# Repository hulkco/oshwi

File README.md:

# Oshwi Badege
This badge is still under development, there are still errors or omissions in the circuit, help is welcome

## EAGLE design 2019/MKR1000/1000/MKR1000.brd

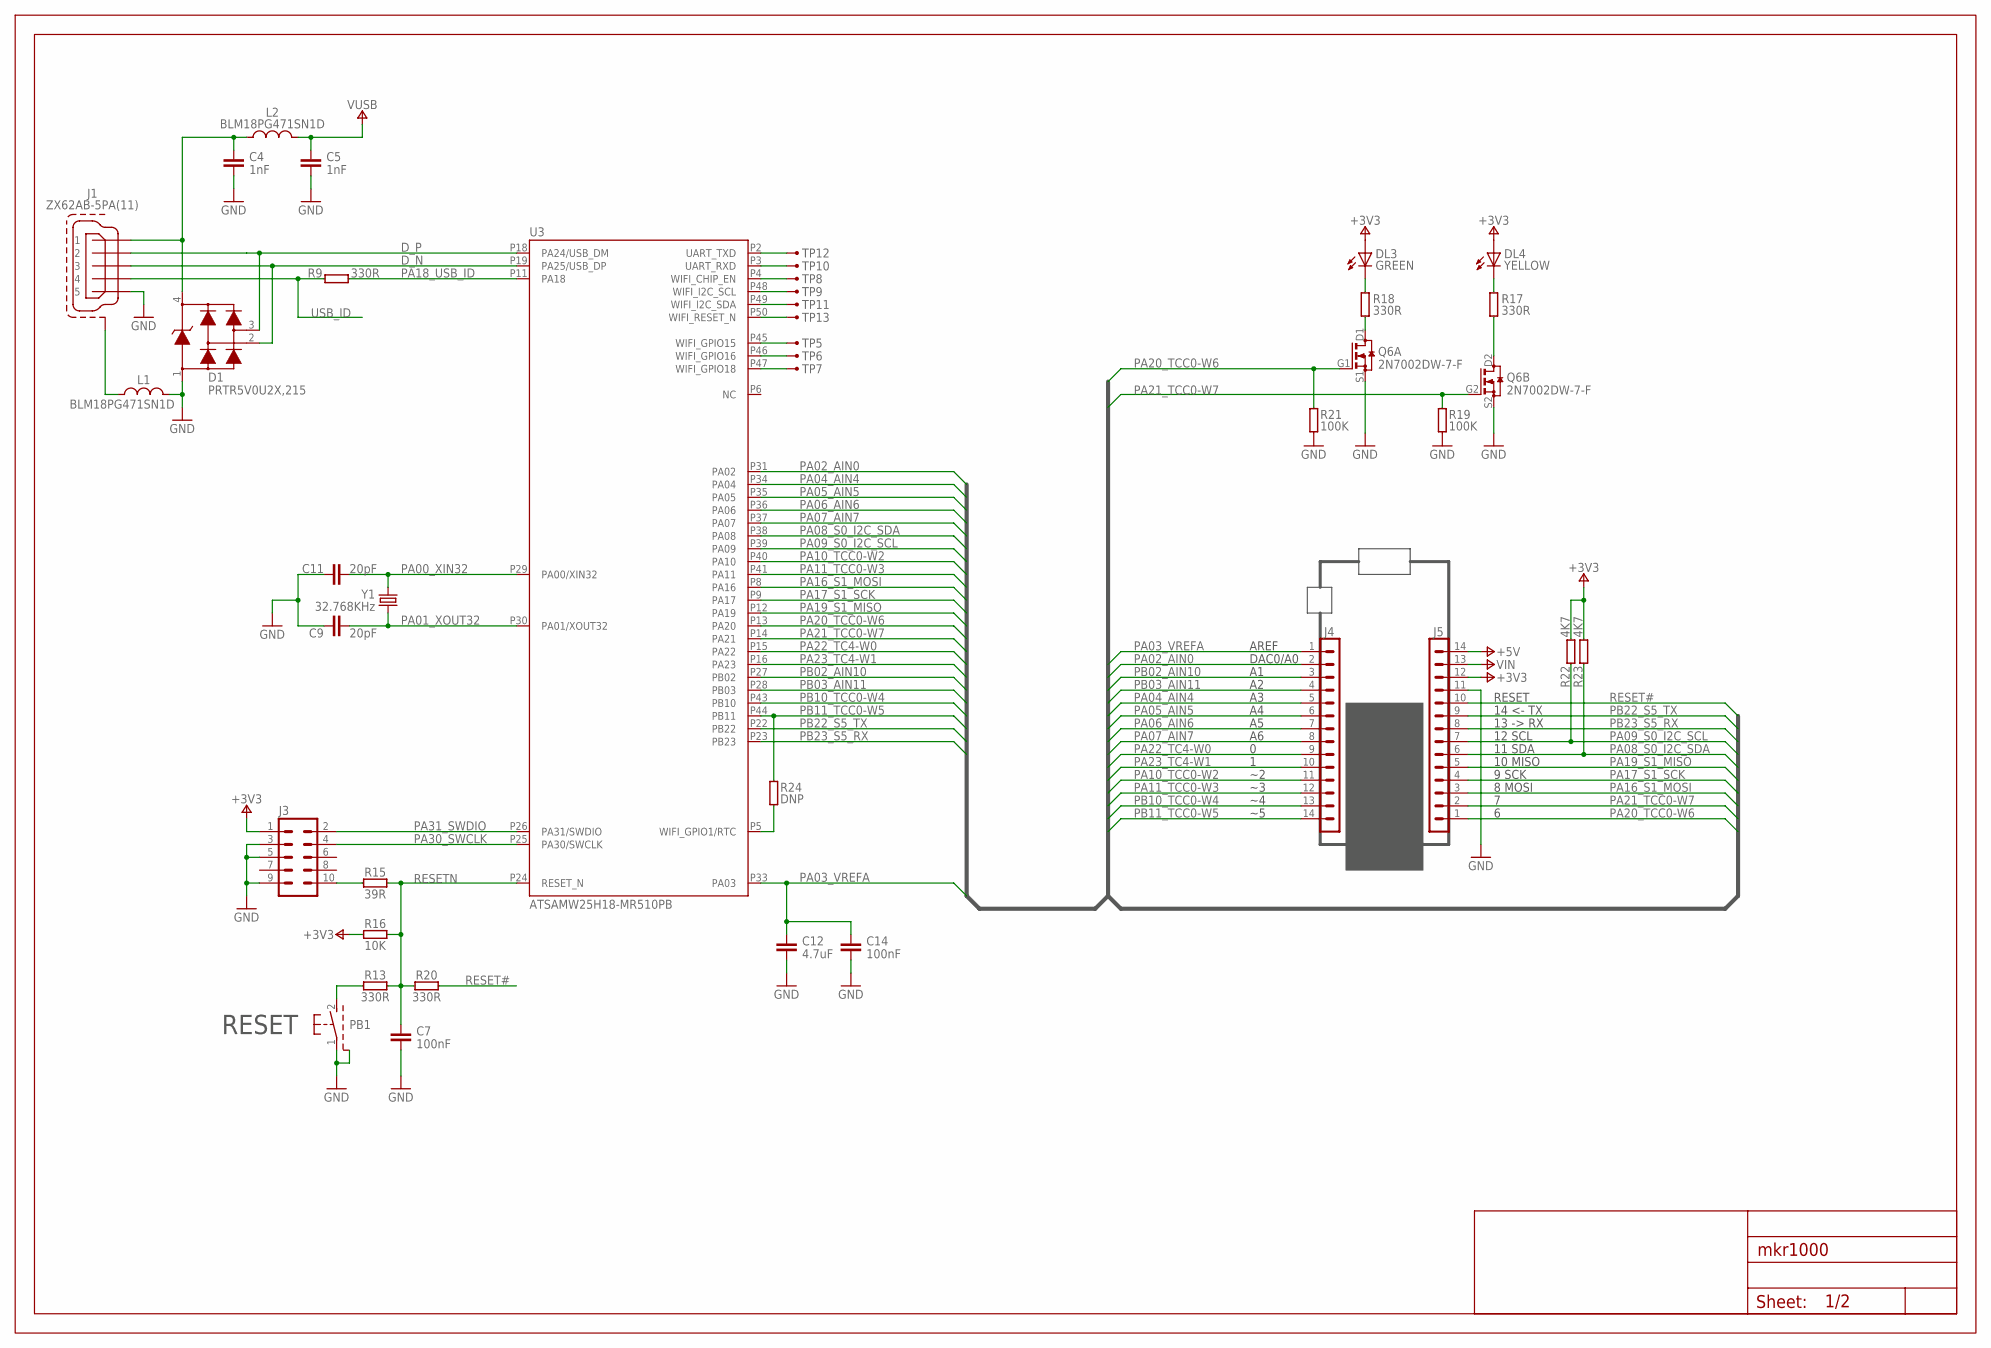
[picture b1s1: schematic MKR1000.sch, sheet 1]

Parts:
C4, C5: 1nF; 0402-1005X55N
C7, C14: 100nF; 0402-1005X55N
C9, C11: 20pF; 0402-1005X55N
C12: 4.7uF; 0402-1005X55N
D1: PRTR5V0U2X,215; SOT190P230X110-4N
DL3: GREEN; LEDC1608X80N-AK
DL4: YELLOW; LEDC1608X80N-AK
FRAME1: DNP; FRAME
J1: ZX62AB-5PA(11); USBMICRO-ZX62-AB-5PA
J3: M50-3600542; FCI-MINITEK127HDR-10
J4, J5: DNP; STRIP-14-MODULI-A11
L1, L2: BLM18PG471SN1D; 0603-1608X90N
PB1: PTS820-20MM; PULS-45X29-PST820
Q6: 2N7002DW-7-F; SOT65P210X110-6AN-DM
R9, R13, R17, R18, R20: 330R; 0402-1005X55N
R15: 39R; 0402-1005X55N
R16: 10K; 0402-1005X55N
R19, R21: 100K; 0402-1005X55N
R22, R23: 4K7; 0402-1005X55N
R24: DNP; 0402-1005X55N
TP5, TP6, TP7, TP8, TP9, TP10, TP11, TP12, TP13: TESTPAD; PAD-SMD
U3: ATSAMW25H18-MR510PB; SAMW25
Y1: 32.768KHz; QUARZO-ABS07

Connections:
+3V3: DL3.A, DL4.A, J3.1, J5.12, R16.1, R22.2, R23.2; also elsewhere on the board
+5V: J5.14; also elsewhere on the board
D_N: D1.2, J1.3, U3.P19 (PA25/USB_DP)
D_P: D1.3, J1.2, U3.P18 (PA24/USB_DM)
GND: C4.2, C5.2, C7.2, C9.1, C11.1, C12.2, C14.2, D1.1, J1.5, J3.3, J3.5, J3.9, J5.11, L1.2, PB1.1, PB1.3 (SH), PB1.4 (SH), PB1.5 (SH), PB1.6 (SH), Q6.S1 (S), Q6.S2 (S), R19.1, R21.1; also elsewhere on the board
N17650912: C4.1, D1.4, J1.1, L2.1
unnamed: R24.1, U3.P5 (WIFI_GPIO1/RTC)
unnamed: DL4.C, R17.2
unnamed: Q6.D2 (D), R17.1
unnamed: Q6.D1 (D), R18.1
unnamed: J3.10, R15.1
unnamed: J1.6 (SH), J1.7 (SH), J1.8 (SH), J1.9 (SH), J1.10 (SH), J1.11 (SH), L1.1
unnamed: PB1.2 (S), R13.1
unnamed: DL3.C, R18.2
PA00_XIN32: C11.2, U3.P29 (PA00/XIN32), Y1.2
PA01_XOUT32: C9.2, U3.P30 (PA01/XOUT32), Y1.1
PA02_AIN0: J4.2, U3.P31 (PA02)
PA03_VREFA: C12.1, C14.1, J4.1, U3.P33 (PA03)
PA04_AIN4: J4.5, U3.P34 (PA04)
PA05_AIN5: J4.6, U3.P35 (PA05)
PA06_AIN6: J4.7, U3.P36 (PA06)
PA07_AIN7: J4.8, U3.P37 (PA07)
PA08_S0_I2C_SDA: J5.6, R23.1, U3.P38 (PA08)
PA09_S0_I2C_SCL: J5.7, R22.1, U3.P39 (PA09)
PA10_TCC0-W2: J4.11, U3.P40 (PA10)
PA11_TCC0-W3: J4.12, U3.P41 (PA11)
PA16_S1_MOSI: J5.3, U3.P8 (PA16)
PA17_S1_SCK: J5.4, U3.P9 (PA17)
PA18_USB_ID: R9.2, U3.P11 (PA18)
PA19_S1_MISO: J5.5, U3.P12 (PA19)
PA20_TCC0-W6: J5.1, Q6.G1 (G), R21.2, U3.P13 (PA20)
PA21_TCC0-W7: J5.2, Q6.G2 (G), R19.2, U3.P14 (PA21)
PA22_TC4-W0: J4.9, U3.P15 (PA22)
PA23_TC4-W1: J4.10, U3.P16 (PA23)
PA30_SWCLK: J3.4, U3.P25 (PA30/SWCLK)
PA31_SWDIO: J3.2, U3.P26 (PA31/SWDIO)
PB02_AIN10: J4.3, U3.P27 (PB02)
PB03_AIN11: J4.4, U3.P28 (PB03)
PB10_TCC0-W4: J4.13, U3.P43 (PB10)
PB11_TCC0-W5: J4.14, R24.2, U3.P44 (PB11)
PB22_S5_TX: J5.9, U3.P22 (PB22)
PB23_S5_RX: J5.8, U3.P23 (PB23)
RESET#: J5.10, R20.2
RESETN: C7.1, R13.2, R15.2, R16.2, R20.1, U3.P24 (RESET_N)
TP5: TP5.1, U3.P45 (WIFI_GPIO15)
TP6: TP6.1, U3.P46 (WIFI_GPIO16)
TP7: TP7.1, U3.P47 (WIFI_GPIO18)
TP8: TP8.1, U3.P4 (WIFI_CHIP_EN)
TP9: TP9.1, U3.P48 (WIFI_I2C_SCL)
TP10: TP10.1, U3.P3 (UART_RXD)
TP11: TP11.1, U3.P49 (WIFI_I2C_SDA)
TP12: TP12.1, U3.P2 (UART_TXD)
TP13: TP13.1, U3.P50 (WIFI_RESET_N)
USB_ID: J1.4, R9.1; also elsewhere on the board
VIN: J5.13; also elsewhere on the board
VUSB: C5.1, L2.2; also elsewhere on the board

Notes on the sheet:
14 <- TX
13 -> RX
12 SCL
RESET
11 SDA
8 MOSI
9 SCK
10 MISO
AREF
DAC0/A0

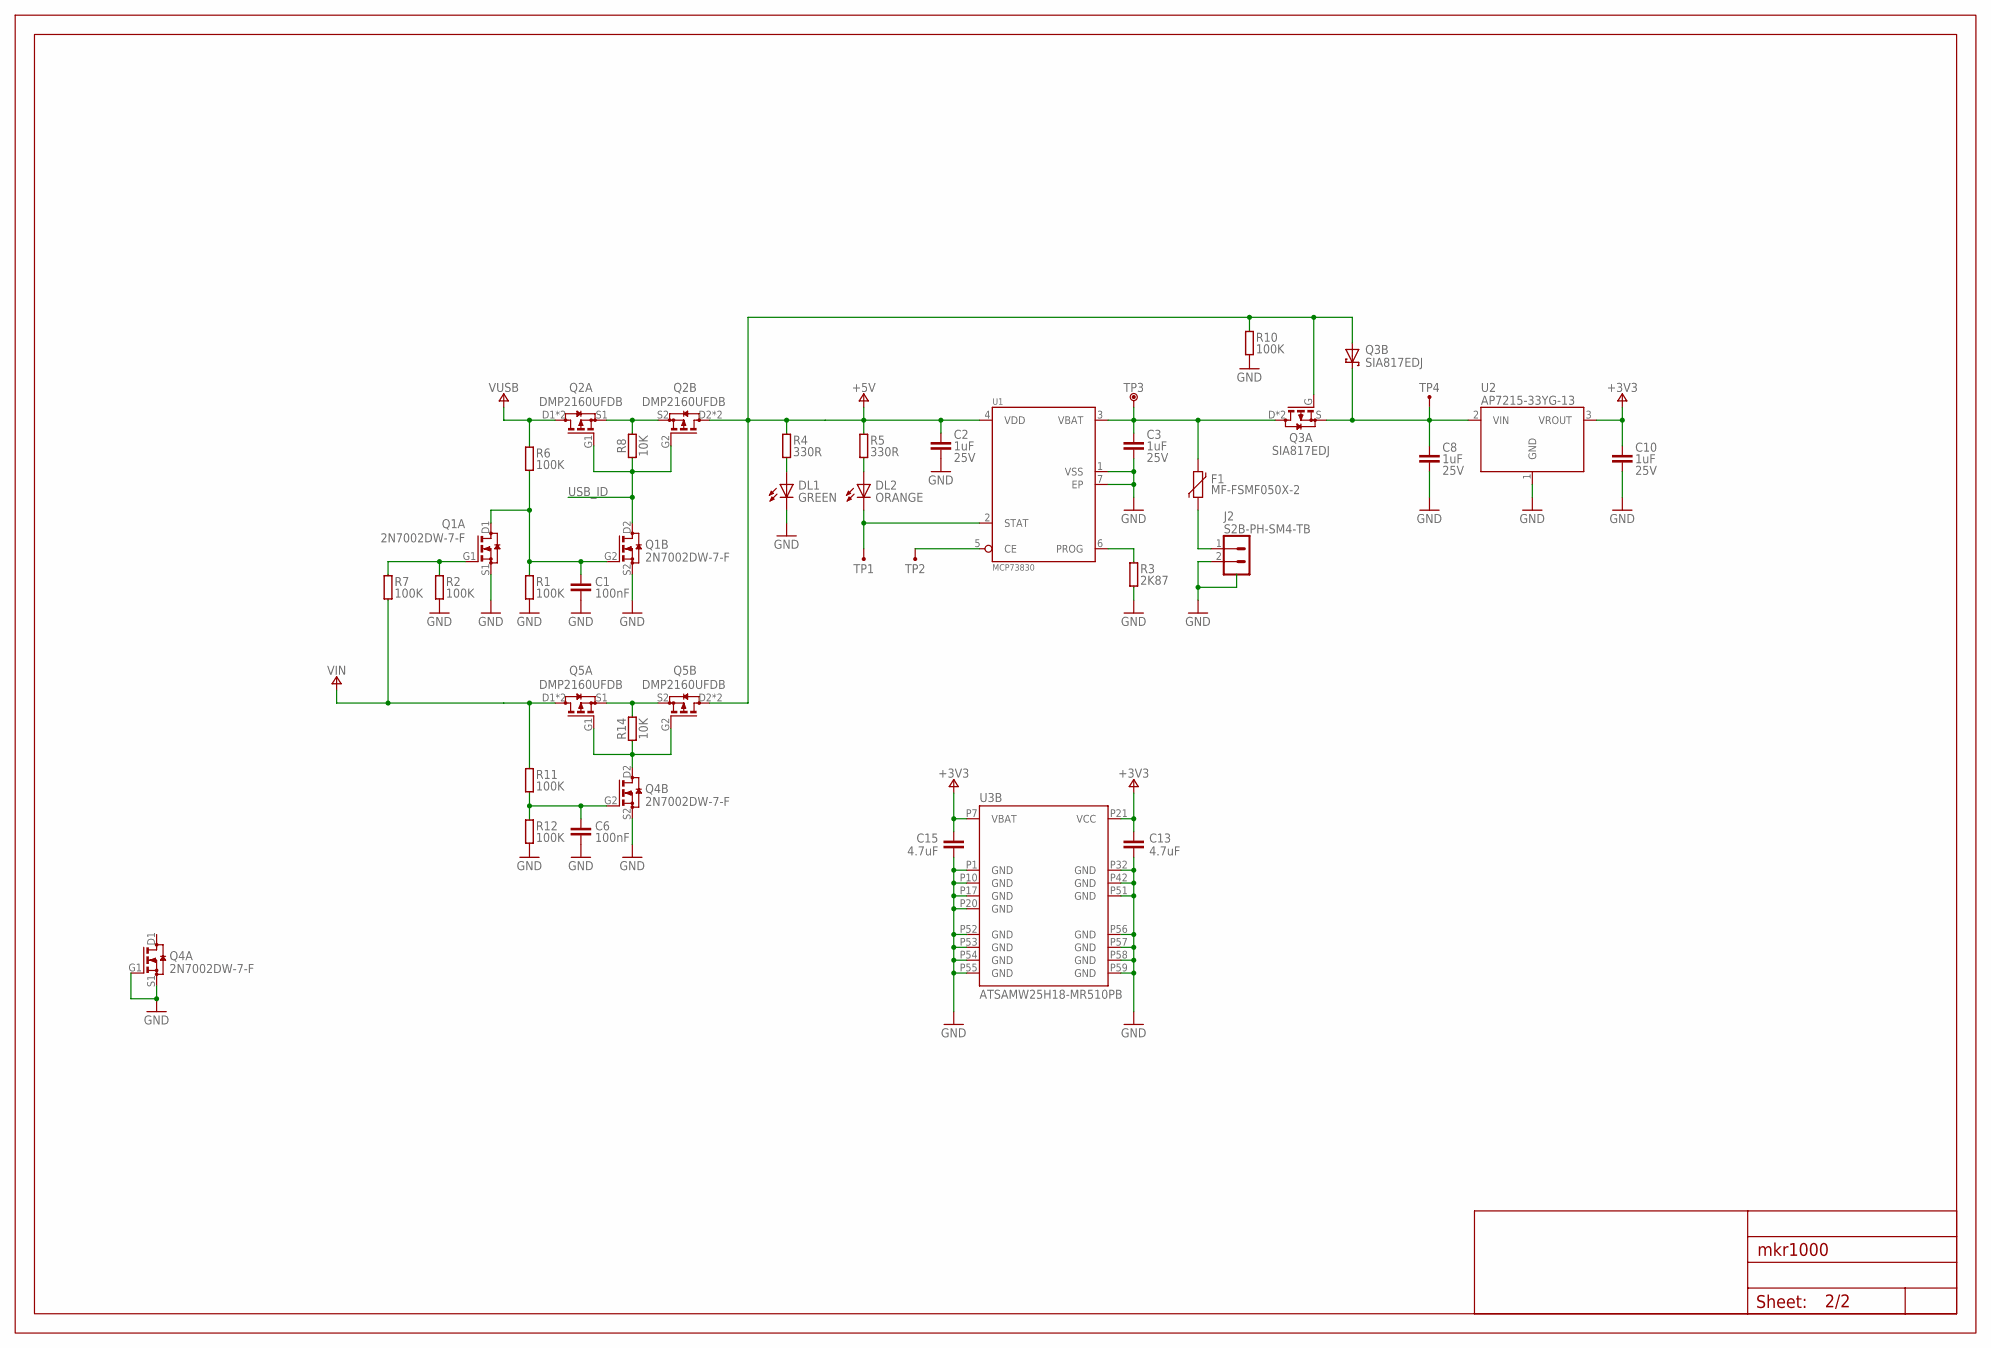
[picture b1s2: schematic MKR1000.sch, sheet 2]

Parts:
C1, C6: 100nF; 0402-1005X55N
C2, C3, C8, C10: 1uF; 0402-1005X55N; VOLTAGE 25V
C13, C15: 4.7uF; 0402-1005X55N
DL1: GREEN; LEDC1608X80N-AK
DL2: ORANGE; LEDC1608X80N-AK
F1: MF-FSMF050X-2; 0603-F1608X100N
FRAME2: Page 2; FRAME-NO-BAN-FRAMEONLY
J2: S2B-PH-SM4-TB; JST-S2B-PH-SM4-TB
Q1, Q4: 2N7002DW-7-F; SOT65P210X110-6AN-DM
Q2, Q5: DMP2160UFDB; SON65P200X200X60-8N-DM
Q3: SIA817EDJ; SON65P205X205X75-8N-MWSD
R1, R2, R6, R7, R10, R11, R12: 100K; 0402-1005X55N
R3: 2K87; 0805-R2013X50N
R4, R5: 330R; 0402-1005X55N
R8, R14: 10K; 0402-1005X55N
TP1, TP2, TP4: TESTPAD; PAD-SMD
TP3: TESTPOINT; TESTPOINT-60MLS-F0_9MM
U1: MCP73830; SON50P200X200X80-7N-EP160X60
U2: AP7215-33YG-13; SOT150P400X160-3N
U3: ATSAMW25H18-MR510PB; SAMW25

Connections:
+3V3: C10.1, C13.1, C15.1, U2.3 (VROUT), U3.P7 (VBAT), U3.P21 (VCC); also elsewhere on the board
+5V: C2.1, Q2.D2 (D), Q2.D2' (D), Q3.A, Q3.G, Q5.D2 (D), Q5.D2' (D), R4.2, R5.2, R10.2, U1.4 (VDD); also elsewhere on the board
GND: C1.2, C2.2, C3.2, C6.2, C8.2, C10.2, C13.2, C15.2, DL1.C, J2.2, J2.3 (SH), J2.4 (SH), Q1.S1 (S), Q1.S2 (S), Q4.G1 (G), Q4.S1 (S), Q4.S2 (S), R1.1, R2.1, R3.1, R10.1, R12.1, U1.1 (VSS), U1.7 (EP), U2.1 (GND), U3.P1 (GND), U3.P10 (GND), U3.P17 (GND), U3.P20 (GND), U3.P32 (GND), U3.P42 (GND), U3.P51 (GND), U3.P52 (GND), U3.P53 (GND), U3.P54 (GND), U3.P55 (GND), U3.P56 (GND), U3.P57 (GND), U3.P58 (GND), U3.P59 (GND); also elsewhere on the board
N17690335: Q2.S1 (S), Q2.S2 (S), R8.2
N17690381: C1.1, Q1.D1 (D), Q1.G2 (G), R1.2, R6.1
N17690428: Q1.G1 (G), R2.2, R7.2
N17690821: Q5.S1 (S), Q5.S2 (S), R14.2
N17690840: Q4.D2 (D), Q5.G1 (G), Q5.G2 (G), R14.1
N17690878: C6.1, Q4.G2 (G), R11.1, R12.2
N17699997: C8.1, Q3.K (C), Q3.K2 (C), Q3.S, TP4.1, U2.2 (VIN)
unnamed: DL2.C, TP1.1, U1.2 (STAT)
unnamed: DL1.A, R4.1
unnamed: R3.2, U1.6 (PROG)
unnamed: DL2.A, R5.1
unnamed: F1.1, J2.1
unnamed: TP2.1, U1.5 (CE)
USB_ID: Q1.D2 (D), Q2.G1 (G), Q2.G2 (G), R8.1; also elsewhere on the board
VBATT: C3.1, F1.2, Q3.D, Q3.D2 (D), TP3.1, U1.3 (VBAT)
VIN: Q5.D1 (D), Q5.D1' (D), R7.1, R11.2; also elsewhere on the board
VUSB: Q2.D1 (D), Q2.D1' (D), R6.2; also elsewhere on the board

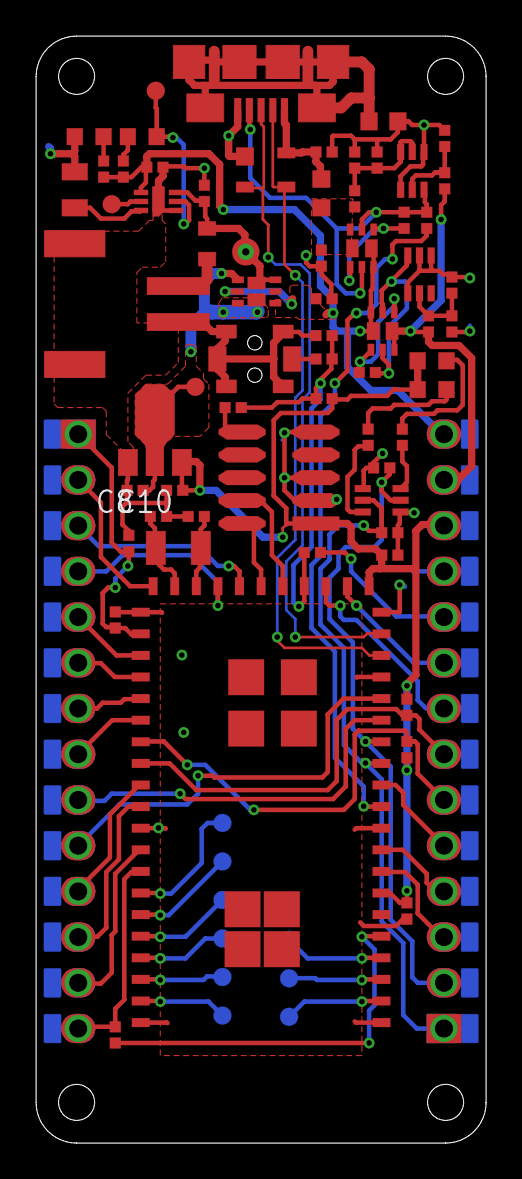
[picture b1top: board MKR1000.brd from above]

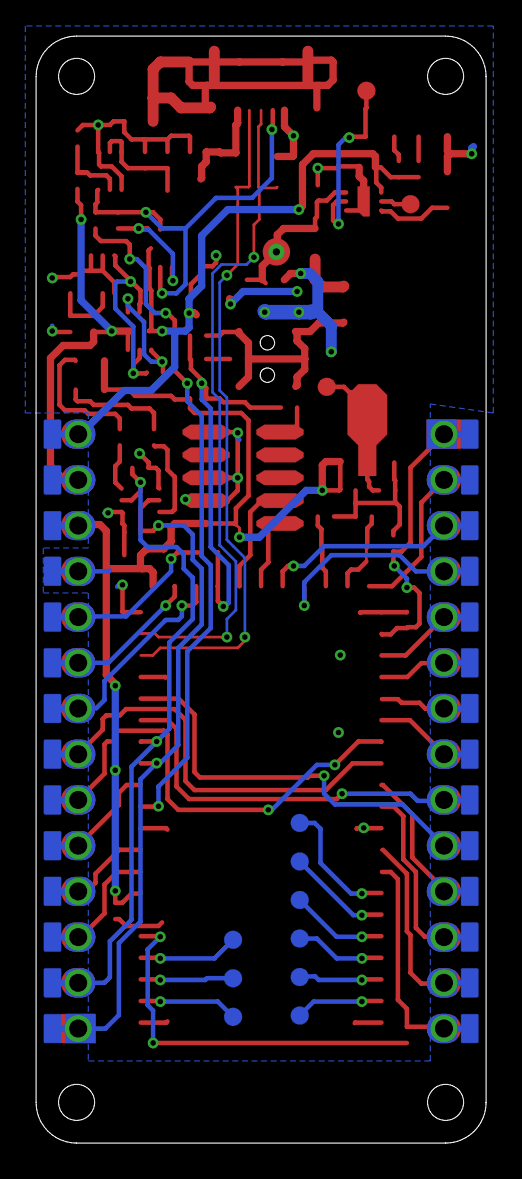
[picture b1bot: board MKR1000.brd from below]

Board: 2 copper layers, 25.0 x 61.5 mm, 78 parts (9 on the bottom side), 70 nets.

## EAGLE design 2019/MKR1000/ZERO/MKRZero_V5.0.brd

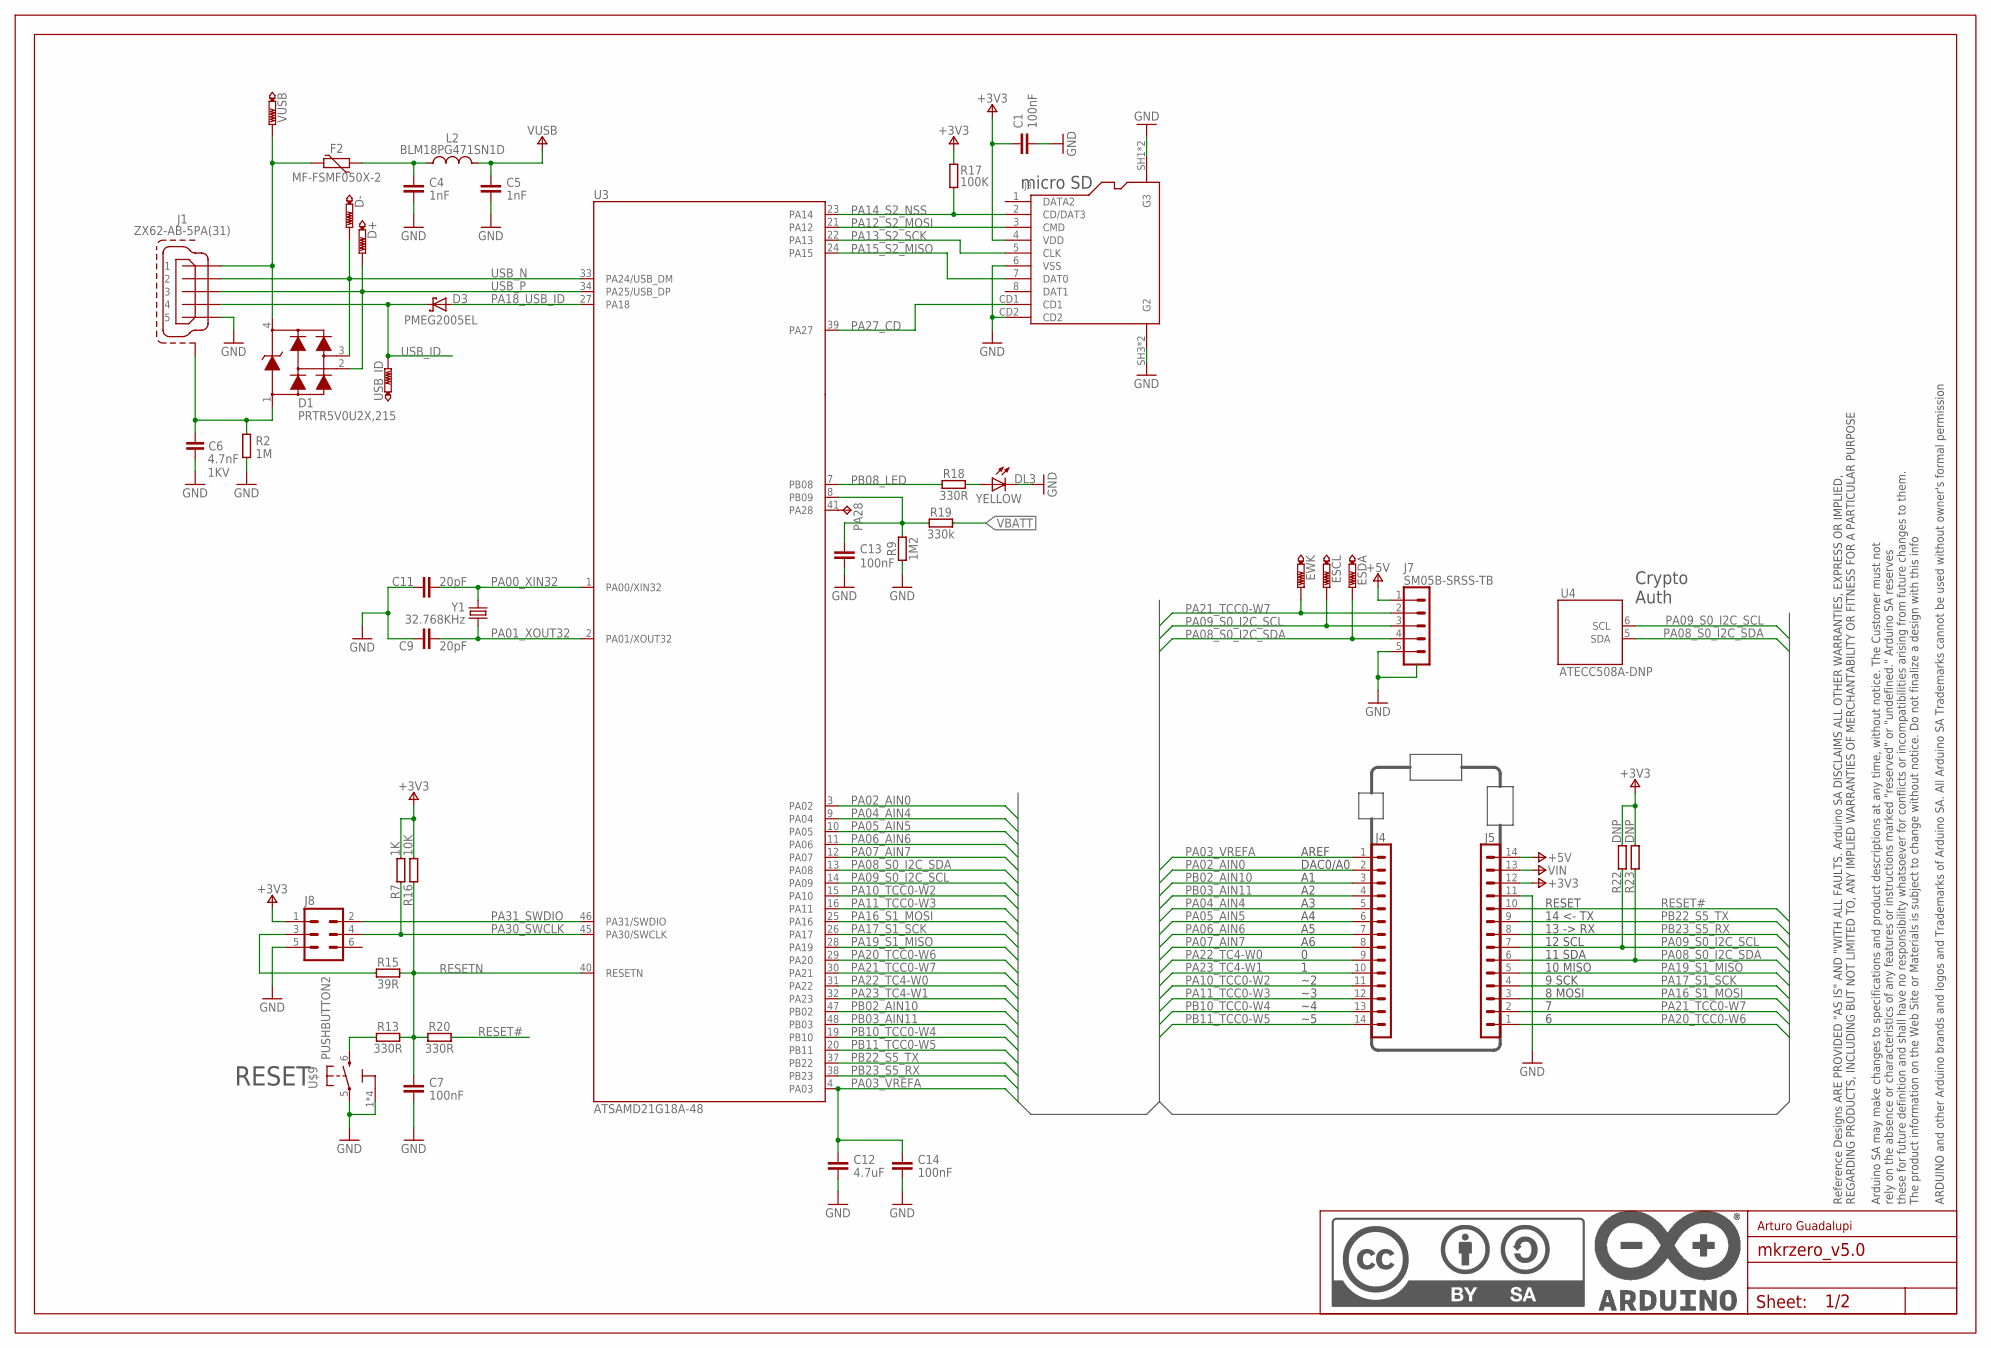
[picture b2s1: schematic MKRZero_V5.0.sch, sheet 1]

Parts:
C1, C7, C13, C14: 100nF; 0402-1005X55N
C4, C5: 1nF; 0402-1005X55N
C6: 4.7nF; C0805; VOLTAGE 1KV
C9, C11: 20pF; 0402-1005X55N
C12: 4.7uF; 0402-1005X55N
D1: PRTR5V0U2X,215; SOT190P230X110-4N
D3: PMEG2005EL; SODFL1008X40N-882D
D+: PTR1B1,27; B1,27
D-: PTR1B1,27; B1,27
DL3: YELLOW; LEDC1608X80N-AK
ESCL: PTR1B1,27; B1,27
ESDA: PTR1B1,27; B1,27
EWK: PTR1B1,27; B1,27
F2: MF-FSMF050X-2; 0603-F1608X100N
FRAME1: DNP; FRAME
J1: ZX62-AB-5PA(31); USBMICRO-ZX62-AB-5PA
J3: AMPHENOL_114-00841-68
J4, J5: DNP; STRIP-14-MODULI-A11
J7: SM05B-SRSS-TB
J8: 2X3_SMD_MALE; 2X3_SMT
L2: BLM18PG471SN1D; 0603-1608X90N
PA28: TPB2,54; B2,54
R2: 1M; 0402-1005X55N
R7: 1K; 0402-1005X55N
R9: 1M2; 0402-1005X55N
R13, R18, R20: 330R; 0402-1005X55N
R15: 39R; 0402-1005X55N
R16: 10K; 0402-1005X55N
R17: 100K; 0402-1005X55N
R19: 330k; 0402-1005X55N
R22, R23: DNP; 0402-1005X55N
U3: ATSAMD21G18A-48; QFN50P700X700X90-49XN-EPSQ515
U4: ATECC508A-DNP; SON50P300X200X60-9N-EP160X140
U$9: PUSHBUTTON2; C&K_PTS820_NOPEGS
USB_ID: PTR1B1,27; B1,27
VUSB: PTR1B1,27; B1,27
Y1: 32.768KHz; QUARZO-ABS07

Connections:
+3V3: C1.1, J3.4 (VDD), J5.12, J8.1, R7.2, R16.2, R17.2, R22.2, R23.2; also elsewhere on the board
+5V: J5.14, J7.1; also elsewhere on the board
GND: C1.2, C4.2, C5.2, C6.2, C7.2, C9.1, C11.1, C12.2, C13.2, C14.2, DL3.C, J1.5, J3.6 (VSS), J3.CD2, J3.SH1 (G3), J3.SH2 (G3), J3.SH3 (G2), J3.SH4 (G2), J5.11, J7.5, J7.SH1 (SH), J7.SH2 (SH), J8.5, R2.1, R9.1, U$9.1 (3), U$9.2 (3), U$9.3, U$9.4 (3), U$9.5 (1); also elsewhere on the board
N17650912: D1.4, F2.2, J1.1, VUSB.PP
N17658775: R13.1, U$9.6 (2)
unnamed: C6.1, D1.1, J1.6 (SH), J1.7 (SH), J1.8 (SH), J1.9 (SH), J1.10 (SH), J1.11 (SH), R2.2
unnamed: C4.1, F2.1, L2.1
unnamed: J8.3, R15.1
unnamed: PA28.PP, U3.41 (PA28)
unnamed: C13.1, R9.2, R19.1, U3.8 (PB09)
unnamed: DL3.A, R18.2
PA00_XIN32: C11.2, U3.1 (PA00/XIN32), Y1.2
PA01_XOUT32: C9.2, U3.2 (PA01/XOUT32), Y1.1
PA02_AIN0: J4.2, U3.3 (PA02)
PA03_VREFA: C12.1, C14.1, J4.1, U3.4 (PA03)
PA04_AIN4: J4.5, U3.9 (PA04)
PA05_AIN5: J4.6, U3.10 (PA05)
PA06_AIN6: J4.7, U3.11 (PA06)
PA07_AIN7: J4.8, U3.12 (PA07)
PA08_S0_I2C_SDA: ESDA.PP, J5.6, J7.4, R23.1, U3.13 (PA08), U4.5 (SDA)
PA09_S0_I2C_SCL: ESCL.PP, J5.7, J7.3, R22.1, U3.14 (PA09), U4.6 (SCL)
PA10_TCC0-W2: J4.11, U3.15 (PA10)
PA11_TCC0-W3: J4.12, U3.16 (PA11)
PA12_S2_MOSI: J3.3 (CMD), U3.21 (PA12)
PA13_S2_SCK: J3.5 (CLK), U3.22 (PA13)
PA14_S2_NSS: J3.2 (CD/DAT3), R17.1, U3.23 (PA14)
PA15_S2_MISO: J3.7 (DAT0), U3.24 (PA15)
PA16_S1_MOSI: J5.3, U3.25 (PA16)
PA17_S1_SCK: J5.4, U3.26 (PA17)
PA18_USB_ID: D3.A, U3.27 (PA18)
PA19_S1_MISO: J5.5, U3.28 (PA19)
PA20_TCC0-W6: J5.1, U3.29 (PA20)
PA21_TCC0-W7: EWK.PP, J5.2, J7.2, U3.30 (PA21)
PA22_TC4-W0: J4.9, U3.31 (PA22)
PA23_TC4-W1: J4.10, U3.32 (PA23)
PA27_CD: J3.CD1, U3.39 (PA27)
PA30_SWCLK: J8.4, R7.1, U3.45 (PA30/SWCLK)
PA31_SWDIO: J8.2, U3.46 (PA31/SWDIO)
PB02_AIN10: J4.3, U3.47 (PB02)
PB03_AIN11: J4.4, U3.48 (PB03)
PB08_LED: R18.1, U3.7 (PB08)
PB10_TCC0-W4: J4.13, U3.19 (PB10)
PB11_TCC0-W5: J4.14, U3.20 (PB11)
PB22_S5_TX: J5.9, U3.37 (PB22)
PB23_S5_RX: J5.8, U3.38 (PB23)
RESET#: J5.10, R20.2
RESETN: C7.1, R13.2, R15.2, R16.1, R20.1, U3.40 (RESETN)
USB_ID: D3.C, J1.4, USB_ID.PP; also elsewhere on the board
USB_N: D1.3, D-.PP, J1.2, U3.33 (PA24/USB_DM)
USB_P: D1.2, D+.PP, J1.3, U3.34 (PA25/USB_DP)
VBATT: R19.2; also elsewhere on the board
VIN: J5.13; also elsewhere on the board
VUSB: C5.1, L2.2; also elsewhere on the board

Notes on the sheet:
14 <- TX
13 -> RX
12 SCL
RESET
11 SDA
8 MOSI
9 SCK
10 MISO
AREF
DAC0/A0
Crypto Auth
micro SD
Arturo Guadalupi

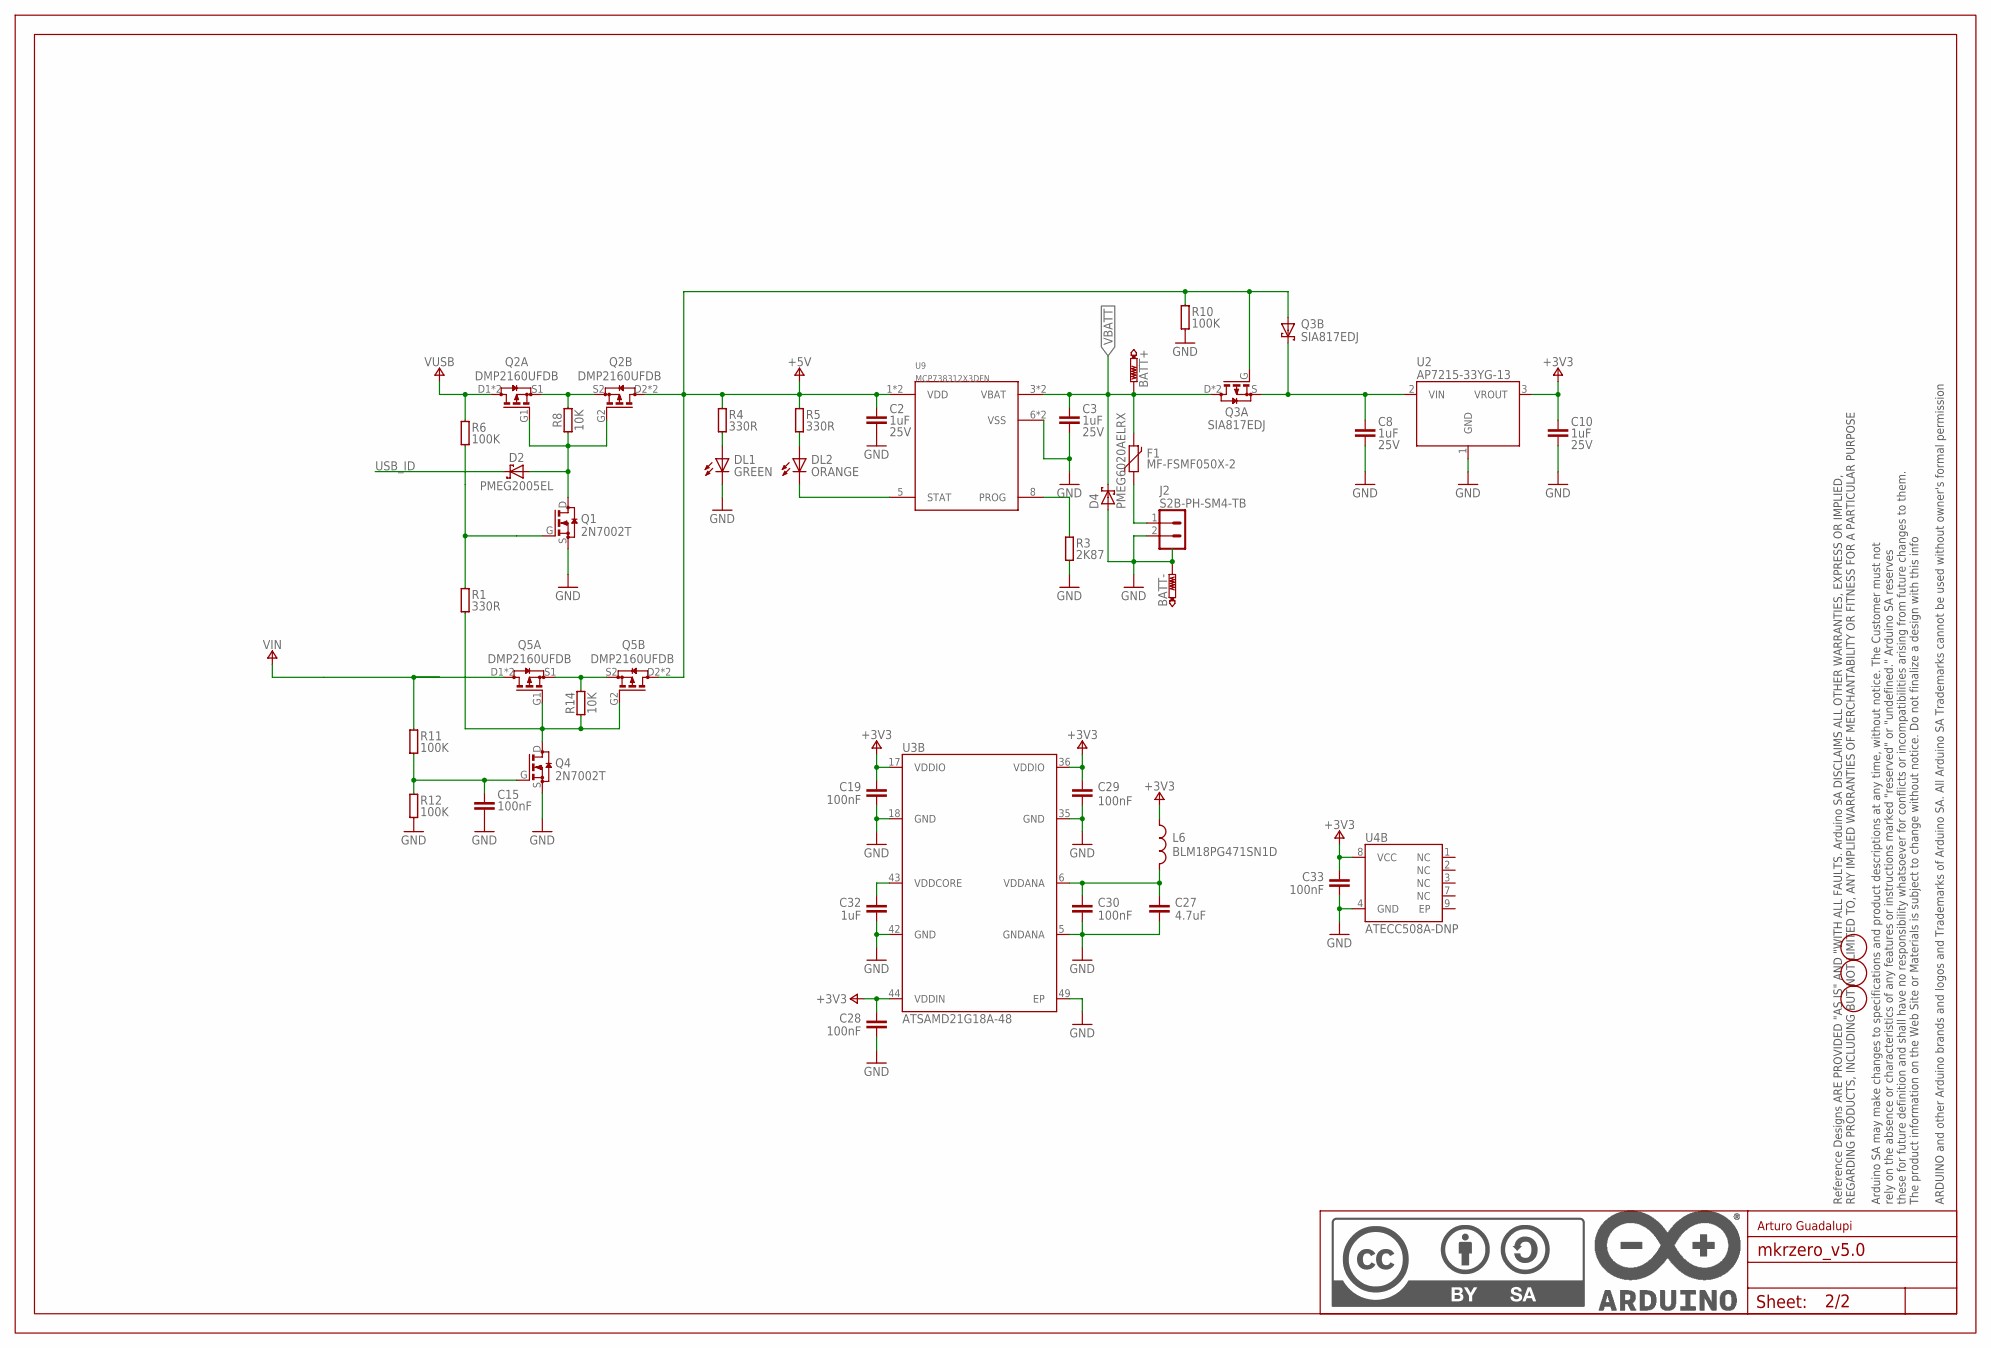
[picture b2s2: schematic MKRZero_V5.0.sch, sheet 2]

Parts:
BATT+: PTR1B1,27; B1,27
BATT-: PTR1B1,27; B1,27
C2, C3, C8, C10: 1uF; 0402-1005X55N; VOLTAGE 25V
C15: 100nF; 0402-1005X55N; VOLTAGE 25V
C19, C28, C29, C30, C33: 100nF; 0402-1005X55N
C27: 4.7uF; 0402-1005X55N
C32: 1uF; 0402-1005X55N
D2: PMEG2005EL; SODFL1008X40N-882D
D4: PMEG6020AELRX; SMA_DO123
DL1: GREEN; LEDC1608X80N-AK
DL2: ORANGE; LEDC1608X80N-AK
F1: MF-FSMF050X-2; 0603-F1608X100N
FD1, FD2, FD3: FIDUCIALMOUNT; FIDUCIAL-MOUNT
FRAME2: DNP; FRAME
J2: S2B-PH-SM4-TB; JST-S2B-PH-SM4-TB
L6: BLM18PG471SN1D; 0603-1608X90N
Q1, Q4: 2N7002T; SOTFL50P160X78-3
Q2, Q5: DMP2160UFDB; SON65P200X200X60-8N-DM
Q3: SIA817EDJ; SON65P205X205X75-8N-MWSD
R1, R4, R5: 330R; 0402-1005X55N
R3: 2K87; 0402-1005X55N
R6, R10, R11, R12: 100K; 0402-1005X55N
R8, R14: 10K; 0402-1005X55N
U2: AP7215-33YG-13; SOT150P400X160-3N
U3: ATSAMD21G18A-48; QFN50P700X700X90-49XN-EPSQ515
U4: ATECC508A-DNP; SON50P300X200X60-9N-EP160X140
U9: MCP738312X3DFN; 2X3DFN

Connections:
+3V3: C10.1, C19.1, C28.1, C29.1, C33.1, L6.1, U2.3 (VROUT), U3.17 (VDDIO), U3.36 (VDDIO), U3.44 (VDDIN), U4.8 (VCC); also elsewhere on the board
+5V: C2.1, Q2.D2 (D), Q2.D2' (D), Q3.A, Q3.G, Q5.D2 (D), Q5.D2' (D), R4.2, R5.2, R10.2, U9.1 (VDD), U9.2 (VDD); also elsewhere on the board
GND: BATT-.PP, C2.2, C3.2, C8.2, C10.2, C15.2, C19.2, C27.2, C28.2, C29.2, C30.2, C32.2, C33.2, D4.A, DL1.C, J2.2, J2.3 (SH), J2.4 (SH), Q1.S, Q4.S, R3.1, R10.1, R12.1, U2.1 (GND), U3.5 (GNDANA), U3.18 (GND), U3.35 (GND), U3.42 (GND), U3.49 (EP), U4.4 (GND), U9.6 (VSS), U9.PAD (VSS); also elsewhere on the board
N17690335: Q2.S1 (S), Q2.S2 (S), R8.2
N17690346: D2.A, Q1.D, Q2.G1 (G), Q2.G2 (G), R8.1
N17690381: Q1.G, R1.2, R6.1
N17690821: Q5.S1 (S), Q5.S2 (S), R14.2
N17690840: Q4.D, Q5.G1 (G), Q5.G2 (G), R1.1, R14.1
N17690878: C15.1, Q4.G, R11.1, R12.2
N17792230: R3.2, U9.8 (PROG)
N17798864: DL2.A, R5.1
N17834267: DL1.A, R4.1
N17852357: C27.1, C30.1, L6.2, U3.6 (VDDANA)
N17852431: C32.1, U3.43 (VDDCORE)
unnamed: F1.1, J2.1
STAT: DL2.C, U9.5 (STAT)
USB_ID: D2.C; also elsewhere on the board
VBATT: BATT+.PP, C3.1, D4.C, F1.2, Q3.D, Q3.D2 (D), U9.3 (VBAT), U9.4 (VBAT); also elsewhere on the board
VIN: Q5.D1 (D), Q5.D1' (D), R11.2; also elsewhere on the board
VLDO: C8.1, Q3.K (C), Q3.K2 (C), Q3.S, U2.2 (VIN)
VUSB: Q2.D1 (D), Q2.D1' (D), R6.2; also elsewhere on the board

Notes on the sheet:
Arturo Guadalupi

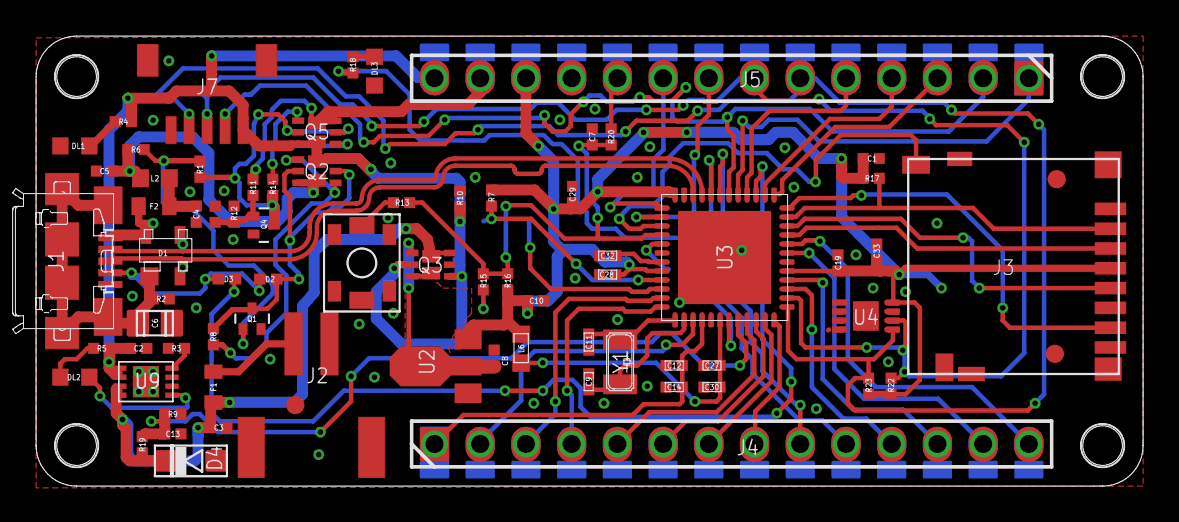
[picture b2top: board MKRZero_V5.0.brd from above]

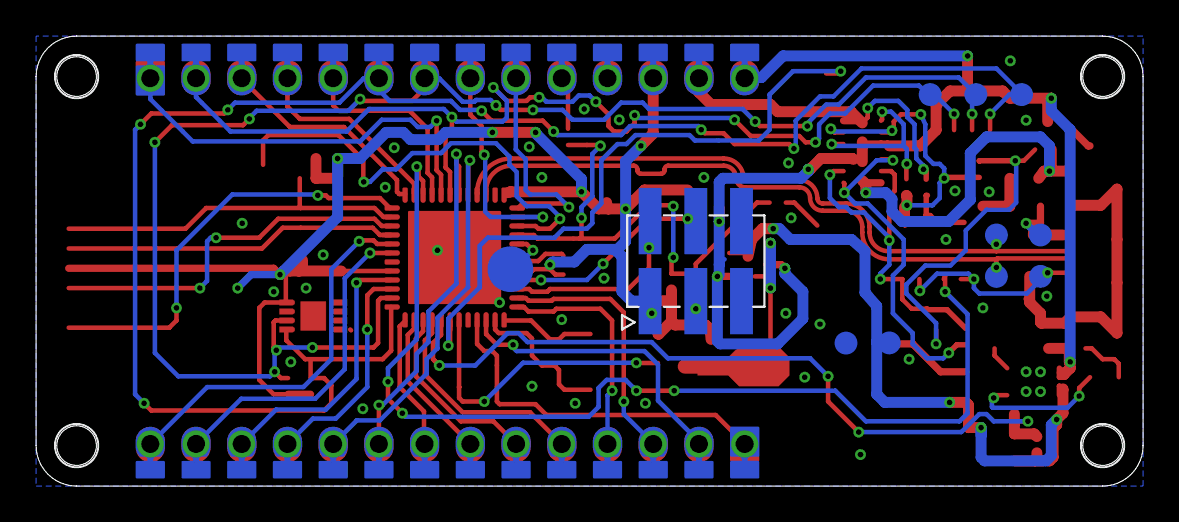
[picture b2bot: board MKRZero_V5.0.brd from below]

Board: 2 copper layers, 61.4 x 24.9 mm, 92 parts (11 on the bottom side), 67 nets.

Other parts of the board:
U$5, U$6, U$7, U$8: MH_RND_F_2.2MM_NM

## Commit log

2017-07-16 :neckbeard: Added .gitattributes & .gitignore files
2017-07-16 Upload
    Just firts upload, remember this a very alpha release
2017-08-01 Some changes
    Add, pull up resistor, capacitors for filtering and routing.
2017-08-12 Final release OSHWDem Badge with PCBWay sponsorship
2017-08-12 Final Release of OSHWDem Badge 2017
    Final Release of OSHWDem Badge with PCBWay sponsorship
2017-08-12 add Libraries
2017-08-12 move to Libraries
2017-08-12 Change Label D2
2017-08-12 update images
2017-08-23 Set theme jekyll-theme-cayman
2017-09-01 Folders version
2017-09-01 Some minors canges
2017-09-01 Some files
2017-09-01 Some changes
2017-09-01 Test
2017-09-01 Upload OshPark Version
2017-09-01 Upload PCBWay Version
2017-09-23 Auto stash before merge of "master" and "origin/master"
2017-09-23 Rev 1
2017-10-15 Changes an add Mazportal version
2018-02-20 Add Schematic PDF
2018-03-04 Add Fritzing Parts
2018-03-19 Update Buttom Reset description
2019-04-27 Move to a year directory
2019-04-27 Update footprints
2019-04-27 Update directory release 2017
2019-04-27 Upload ArtWork to release 2017
2019-04-29 Update schematic
2019-04-29 Update directory tft name
2019-04-29 Add Schematic for TFT & PyPortal
2019-04-29 Minors updates
2019-05-03 More examples TFTs
2019-05-07 Add Flash Breakout
2019-05-13 Minor updates
2019-05-20 Update Nano
2019-05-20 Add Info TFT
2019-05-22 Remove Bad commits & Update SPI Symbol
2019-05-22 Update SAMD21G Symbol & add CE schematic
2019-05-22 Add CE Symbol
2019-05-23 Update Schematic SAMD21G & SPI
2019-05-23 Add tft-shield project
2019-05-24 Add Draw settings in Docs TFT
2019-05-27 Change Directory structure
2019-05-28 Add OshwiM0 resumen
2019-05-28 Update Symbol MicroUSB
2019-06-11 Add Changes to Oshwi 2019 Badge
2019-06-14 Add changes tft_shield
2019-06-15 Add some changess & 3d model
2019-06-15 Update 3d Model
2019-06-16 Create TFT Library
2019-06-16 Various updates
2019-06-18 Add Arduino Code for Generic TFT 0.96
2019-06-26 Add SPI Bus Doctos
2019-06-27 Changes MicroSD
2019-06-27 Add ESP32 pinout
2019-06-27 Move TFT pinout because Micro SD problem
2019-06-28 Add Bast SERCOM PinOut
2019-07-08 Add new Docs to Library
2019-07-08 Minor changes Micro SD pinout
2019-07-09 Update ArtWork Oshwi
2019-07-10 Add ESP32 Pico Docs
2019-07-11 Add OshwiESP32 2019
2019-07-12 Add WS2812B-2020 footprint
2019-07-14 Add changes to ArtWork 2019
2019-07-18 Continue the Design of ESP32 Badge
2019-07-22 update es8266 design

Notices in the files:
parts and their libraries:
Arduino-utility: Copyright (c) 2016-2017 Arduino LLC.  All right reserved.
Arduino-utility: This file is licensed under : CC-SA-BY-NC
